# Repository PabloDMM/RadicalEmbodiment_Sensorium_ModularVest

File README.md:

# Sensorium_ModularVest
***Sensorium (Radical Embodiment)*** is a project consisting in a modular illuminated vest that can display abstract information.

***This Repository contains all the files needed to reproduce the device.***
***This Repository is merely destined to the technological part of the project.***
***This Repository makes use of the programs: EagleCad, Arduino IDE, Tensorflow.***

If any other information is needed, please contact with the repository owner (pablodmm.isp@gmail.com) or any of the participants of the project.

## Description

Sensorium is the first prototype for the material tech part of the final project of Gabriel G. Regués. It consist on a modular illuminated vest conformed by an unespecific number of *Arduino* based modules connected to display specific information through an I2C net.

***Watch the Video by pressing the header:***

As escribed in the final essay:

*Sensorium - Radical Embodiment - es un proyecto colectivo desarrollado en colaboración por Jaime Remirez de Ganuza, Gonzalo de Torres Sainz, Pablo de Miguel Morales y Gabriel G. Regües.
Este proyecto es una continuación de un proyecto anterior realizado a finales del 2018 por Jaime y Gabriel, al que llamaron El Culto de la Subversión1 y en el que se formularon algunas preguntas que siguen formando parte de este trabajo. El Culto de la Subversión se enfrentaba a la idea de un grupo social en el que se había impuesto una prenda única y se especulaba sobre las posibilidades de transformación de la misma, a medida que los integrantes entraban o dejaban de formar parte del grupo. Los diseñadores investigaban de qué manera cada individuo podía servir creativamente a la creación de los símbolos de representación de un colectivo organizado de forma igualitaria y horizontal. El proyecto se articuló en torno a la creación de una prenda modular, formada por un número determinado de piezas que podían combinarse de distintas maneras. Estas piezas estaban formadas en tela, en la que habían sido impresos unos elementos gráficos. La posibilidades de reconfiguración de la prenda daban lugar a distintas variaciones, tanto en el aspecto formal como gráfico, que representaban la integración o salida de individuos en el grupo.*

## System Overview

The system is based on a I2C net of *Arduino Nano* based modules that control 10 WS212B RGB LEDs each. The aim is to display abstract information incoming from a *Tensorflow* software system running on a PC based on global population database.

### Arduino Modules

The Arduino Modules are named *IED_GR_Module_Rev_02*. It consist on a triangular PCB equipped with an *Arduino Nano*, a I2C identification resistor array (8bit based, 254 possible directions) and 10 WS2812B RGB LEDs.

Aditionally, it has 3 redundant pairs of miniUSB connectors (both male and female) destined to interconnect an undefined number of modules. The signals present in this connectors are:

* 5V (VCC)
* GND
* SDA (I2C)
* SCL (I2C)

#### Bill of Materials (BOM)
The Module is conformed by the following elements:

* PCB				1	Printed-Circuit-Board	
* Arduino Nano		1	Microprocesador	
* WS2812b  SMD5050	10	RGB LEDs	WS2812B
* Mini USB B female	3	Mini USB B female	
* Mini USB B male	3	Mini USB B male	
* R_DIR_[0:7]		7	10kOhm Resistor. Footprint 1206. Sets the I2C device direction.	
* R_I2C_[0:1]		2	10kOhm Resistor. Footprint 1206. I2C Bus PullUps	

#### PCB Characterictics
The Characteristics of the PCB are the following:

* Dimensions (Square):  100 x 87 mm
* Thickness:            1.6 mm
* Layers:               2 (TOP y BOT)
* Color PCB:            White
* Color Serigraphy:     Black

The PCBs were made through *Elecrow* ( https://www.elecrow.com/ )

#### Prototype Problems
The prototypes have a number of critical mistakes, that can be fixed through the following procedure:

* Step 1: Cut the Signal marked in Blue thorugh the points indicated.
* Step 2: Bypass the signal marked in Green.

Anycase, if anyone plans to rebuild the devices, we strongly encourage to contact us to apply a large number of fixes.

#### Software
The modules make use of two *Arduino* sowfwares, one for *I2C Slave* and another for *I2C Master*:

* _SEN_ModuleI2cMaster.ino_: Distributed a long array of data incoming for USB Serial *Tensorflow* Software running in a PC. Only One module of the net performs as *Master*.

* _SEN_ModuleI2cSlave.ino_: Manages 10 WS2812B REG LEDs based of I2C incoming Data.

Additionally, a large number of preliminary *Arduino* programs can be found in the repository, as part of the development.

Please notice the Arduino Nano used need the *Old ATMega328 Bootloader*, not the new one.

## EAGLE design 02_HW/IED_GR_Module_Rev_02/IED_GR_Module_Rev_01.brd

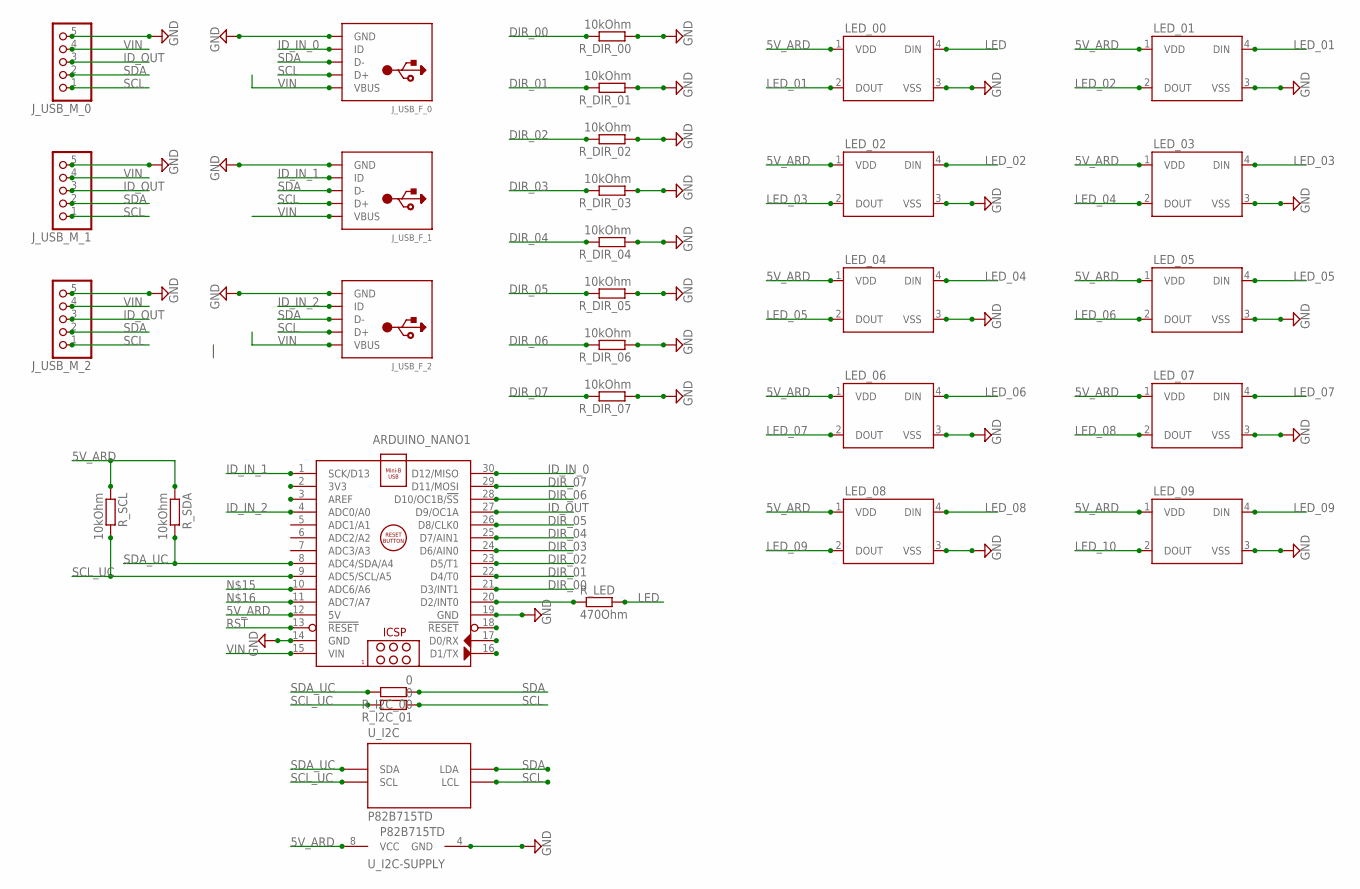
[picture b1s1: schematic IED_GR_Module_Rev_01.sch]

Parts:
ARDUINO_NANO1: ARDUINO_NANO
J_USB_F_0, J_USB_F_1, J_USB_F_2: USBTHM; USB-MINIB-THM
J_USB_M_0, J_USB_M_1, J_USB_M_2: HEADER-1X51.27MM; 1X05_1.27MM
LED_00, LED_01, LED_02, LED_03, LED_04, LED_05, LED_06, LED_07, LED_08, LED_09: WS2812B
R_DIR_00, R_DIR_01, R_DIR_02, R_DIR_03, R_DIR_04, R_DIR_05, R_DIR_06, R_DIR_07: 10kOhm; R1206
R_I2C_00, R_I2C_01: 0; R1206
R_LED: 470Ohm; R1206
R_SCL: 10kOhm; R1206
R_SDA: 10kOhm; R1206
U_I2C: P82B715TD; SOIC-8

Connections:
5V_ARD: ARDUINO_NANO1.12 (5V), LED_00.1 (VDD), LED_01.1 (VDD), LED_02.1 (VDD), LED_03.1 (VDD), LED_04.1 (VDD), LED_05.1 (VDD), LED_06.1 (VDD), LED_07.1 (VDD), LED_08.1 (VDD), LED_09.1 (VDD), R_SCL.1, R_SDA.1, U_I2C.8 (VCC)
DIR_00: ARDUINO_NANO1.21 (D3/INT1), R_DIR_00.2
DIR_01: ARDUINO_NANO1.22 (D4/T0), R_DIR_01.2
DIR_02: ARDUINO_NANO1.23 (D5/T1), R_DIR_02.2
DIR_03: ARDUINO_NANO1.24 (D6/AIN0), R_DIR_03.2
DIR_04: ARDUINO_NANO1.25 (D7/AIN1), R_DIR_04.2
DIR_05: ARDUINO_NANO1.26 (D8/CLK0), R_DIR_05.2
DIR_06: ARDUINO_NANO1.28 (D10/OC1B/!SS), R_DIR_06.2
DIR_07: ARDUINO_NANO1.29 (D11/MOSI), R_DIR_07.2
GND: ARDUINO_NANO1.14 (GND), ARDUINO_NANO1.19 (GND), J_USB_F_0.GND, J_USB_F_1.GND, J_USB_F_2.GND, J_USB_M_0.5, J_USB_M_1.5, J_USB_M_2.5, LED_00.3 (VSS), LED_01.3 (VSS), LED_02.3 (VSS), LED_03.3 (VSS), LED_04.3 (VSS), LED_05.3 (VSS), LED_06.3 (VSS), LED_07.3 (VSS), LED_08.3 (VSS), LED_09.3 (VSS), R_DIR_00.1, R_DIR_01.1, R_DIR_02.1, R_DIR_03.1, R_DIR_04.1, R_DIR_05.1, R_DIR_06.1, R_DIR_07.1, U_I2C.4 (GND)
ID_IN_0: ARDUINO_NANO1.30 (D12/MISO), J_USB_F_0.ID
ID_IN_1: ARDUINO_NANO1.1 (SCK/D13), J_USB_F_1.ID
ID_IN_2: ARDUINO_NANO1.4 (ADC0/A0), J_USB_F_2.ID
ID_OUT: ARDUINO_NANO1.27 (D9/OC1A), J_USB_M_0.3, J_USB_M_1.3, J_USB_M_2.3
LED: LED_00.4 (DIN), R_LED.2
LED_01: LED_00.2 (DOUT), LED_01.4 (DIN)
LED_02: LED_01.2 (DOUT), LED_02.4 (DIN)
LED_03: LED_02.2 (DOUT), LED_03.4 (DIN)
LED_04: LED_03.2 (DOUT), LED_04.4 (DIN)
LED_05: LED_04.2 (DOUT), LED_05.4 (DIN)
LED_06: LED_05.2 (DOUT), LED_06.4 (DIN)
LED_07: LED_06.2 (DOUT), LED_07.4 (DIN)
LED_08: LED_07.2 (DOUT), LED_08.4 (DIN)
LED_09: LED_08.2 (DOUT), LED_09.4 (DIN)
LED_10: LED_09.2 (DOUT)
LED_OUT: ARDUINO_NANO1.20 (D2/INT0), R_LED.1
RST: ARDUINO_NANO1.13 (!RESET)
SCL: J_USB_F_0.D+, J_USB_F_1.D+, J_USB_F_2.D+, J_USB_M_0.1, J_USB_M_1.1, J_USB_M_2.1, R_I2C_01.1, U_I2C.2 (LCL)
SCL_UC: ARDUINO_NANO1.9 (ADC5/SCL/A5), R_I2C_01.2, R_SCL.2, U_I2C.3 (SCL)
SDA: J_USB_F_0.D-, J_USB_F_1.D-, J_USB_F_2.D-, J_USB_M_0.2, J_USB_M_1.2, J_USB_M_2.2, R_I2C_00.1, U_I2C.7 (LDA)
SDA_UC: ARDUINO_NANO1.8 (ADC4/SDA/A4), R_I2C_00.2, R_SDA.2, U_I2C.6 (SDA)
VIN: ARDUINO_NANO1.15 (VIN), J_USB_F_0.VBUS, J_USB_F_1.VBUS, J_USB_F_2.VBUS, J_USB_M_0.4, J_USB_M_1.4, J_USB_M_2.4

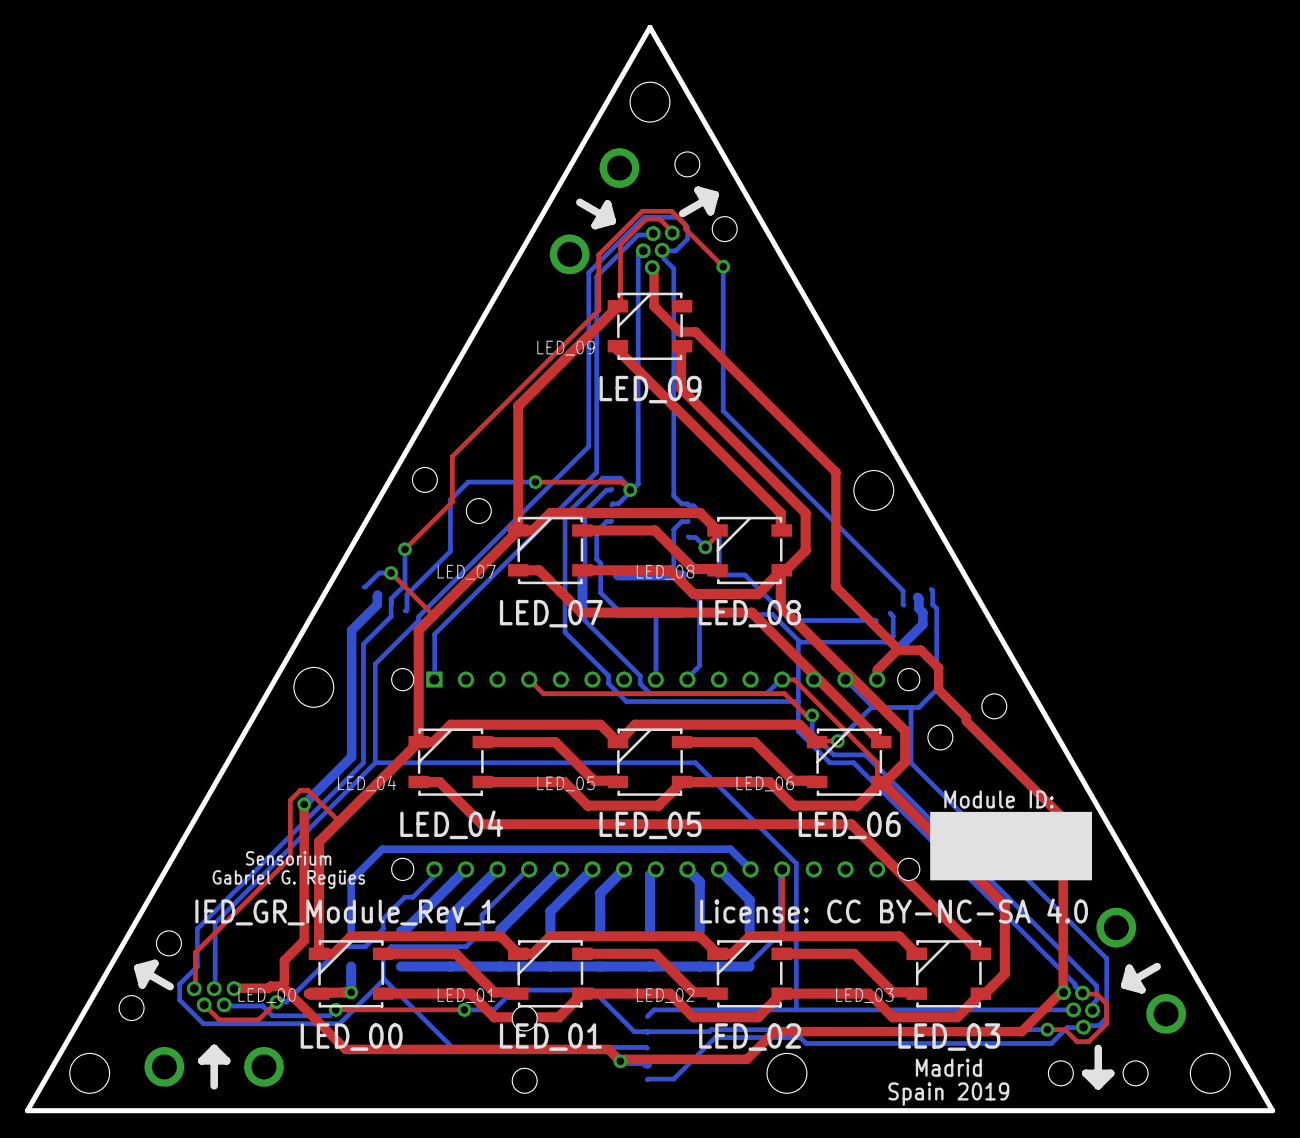
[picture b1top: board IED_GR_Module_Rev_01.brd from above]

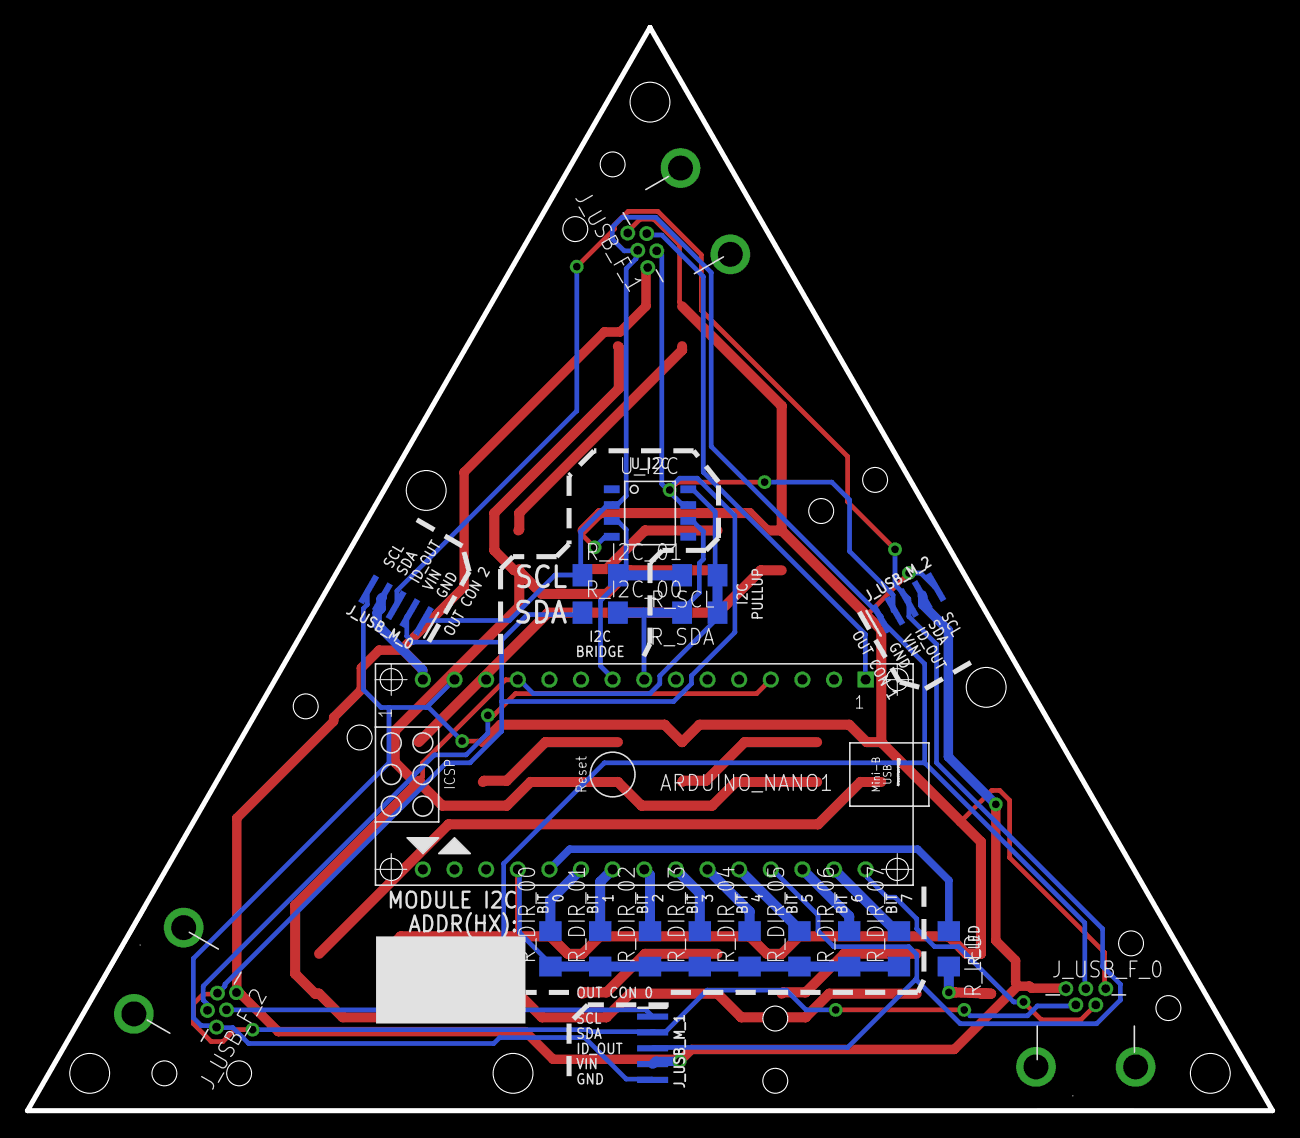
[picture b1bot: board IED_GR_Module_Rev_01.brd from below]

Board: 2 copper layers, 100.0 x 87.0 mm, 31 parts (21 on the bottom side), 30 nets.

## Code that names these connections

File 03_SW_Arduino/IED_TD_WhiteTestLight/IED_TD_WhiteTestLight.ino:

// Libraries
#include <Adafruit_NeoPixel.h>

// Pin definition
const int LED_PIN    = 2;
const int DIR_00_PIN = 3;
const int DIR_01_PIN = 4;
const int DIR_02_PIN = 5;
const int DIR_03_PIN = 6;
const int DIR_04_PIN = 7;
const int DIR_05_PIN = 8;
const int DIR_06_PIN = 10;
const int DIR_07_PIN = 11;

// Program constant values
const int LED_Q      = 10;
// Generated Structures (struct)
struct LEDCOL{
  int red;
  int green;
  int blue;
};
const bool ON                 =   1;         // General ON value
const bool OFF                =   0;         // General OFF value

const bool UP                 =   1;         // General UP Fade Direction value
const bool DOWN               =   0;         // General DOWN Fade Direction value

const int LED_INNER_Q        =   1;         
const int LED_OUTER_Q        =   9;

const int FADESTEPS_C         =   100; // GENERAL FadeSteps
const int FADEDELAY_C         =   100; // GENERAL FadeDelay

const int INNER_LED[LED_INNER_Q]  = {5};
const int OUTER_LED[LED_OUTER_Q]  = {0, 1, 2, 3, 4, 6, 7, 8, 9};

// Gamma Correction (GC) LUT
const byte GC[256] = {
    0,  0,  0,  0,  0,  0,  0,  0,  0,  0,  0,  0,  0,  0,  0,  0,
    0,  0,  0,  0,  0,  0,  0,  0,  0,  0,  0,  0,  1,  1,  1,  1,
    1,  1,  1,  1,  1,  1,  1,  1,  1,  2,  2,  2,  2,  2,  2,  2,
    2,  3,  3,  3,  3,  3,  3,  3,  4,  4,  4,  4,  4,  5,  5,  5,
    5,  6,  6,  6,  6,  7,  7,  7,  7,  8,  8,  8,  9,  9,  9, 10,
   10, 10, 11, 11, 11, 12, 12, 13, 13, 13, 14, 14, 15, 15, 16, 16,
   17, 17, 18, 18, 19, 19, 20, 20, 21, 21, 22, 22, 23, 24, 24, 25,
   25, 26, 27, 27, 28, 29, 29, 30, 31, 32, 32, 33, 34, 35, 35, 36,
   37, 38, 39, 39, 40, 41, 42, 43, 44, 45, 46, 47, 48, 49, 50, 50,
   51, 52, 54, 55, 56, 57, 58, 59, 60, 61, 62, 63, 64, 66, 67, 68,
   69, 70, 72, 73, 74, 75, 77, 78, 79, 81, 82, 83, 85, 86, 87, 89,
   90, 92, 93, 95, 96, 98, 99,101,102,104,105,107,109,110,112,114,
  115,117,119,120,122,124,126,127,129,131,133,135,137,138,140,142,
  144,146,148,150,152,154,156,158,160,162,164,167,169,171,173,175,
  177,180,182,184,186,189,191,193,196,198,200,203,205,208,210,213,
  215,218,220,223,225,228,231,233,236,239,241,244,247,249,252,255 };

LEDCOL GEN_ON    = {GC[255], GC[255],  GC[255]};  
LEDCOL GEN_OFF   = {GC[0],   GC[0],     GC[0]}; 


// Global Variables
Adafruit_NeoPixel LEDSTR = Adafruit_NeoPixel(LED_Q, LED_PIN, NEO_GRB + NEO_KHZ800);
bool fadeDirection = UP;


// IMPORTANT: To reduce NeoPixel burnout risk, add 1000 uF capacitor across
// pixel power leads, add 300 - 500 Ohm resistor on first pixel's data input
// and minimize distance between Arduino and first pixel.  Avoid connecting
// on a live circuit...if you must, connect GND first.

void setup() {
  Serial.begin(115200); // Baudrate Set
  LEDSTR.begin();
  LEDSTR.show(); // Initialize all pixels to 'off'
}

void loop() {
  for(int currentStep = 0; currentStep < FADESTEPS_C; currentStep++){
    LED_GLOWOUT(GEN_ON, GEN_OFF, FADESTEPS_C, (FADEDELAY_C/5), currentStep, fadeDirection);
  }
  fadeDirection = !fadeDirection;   // Switch Fade Glow Direction
}

void LED_GLOWOUT(LEDCOL COL_ON, LEDCOL COL_OFF, int FS, int FD, int Step, bool fadeDir){
  int RDiff = (COL_OFF.red-COL_ON.red);
  int GDiff = (COL_OFF.green-COL_ON.green);
  int BDiff = (COL_OFF.blue-COL_ON.blue);
  //for(int Step = 0; Step < FS; Step++){
  if(fadeDir == UP){
    for(int i = 0; i < LED_INNER_Q; i++){
      //Serial.println(i);
      LEDSTR.setPixelColor(INNER_LED[i], (COL_OFF.green - ((GDiff/FS)*(FS-Step))), (COL_OFF.red - ((RDiff/FS)*(FS-Step))), (COL_OFF.blue - ((BDiff/FS)*(FS-Step))));
    }
    for(int i = 0; i < LED_OUTER_Q; i++){
      //Serial.println(i);
      LEDSTR.setPixelColor(OUTER_LED[i], (COL_OFF.green - ((GDiff/FS)*(Step))), (COL_OFF.red - ((RDiff/FS)*(Step))), (COL_OFF.blue - ((BDiff/FS)*(Step))));
    }
    LEDSTR.show(); // Update LEDs 
    delay(FD);
  }

  else if(fadeDir == DOWN){
    for(int i = 0; i < LED_INNER_Q; i++){
      //Serial.println(i);
      LEDSTR.setPixelColor(INNER_LED[i], (COL_OFF.green - ((GDiff/FS)*(Step))), (COL_OFF.red - ((RDiff/FS)*(Step))), (COL_OFF.blue - ((BDiff/FS)*(Step))));
    }
    for(int i = 0; i < LED_OUTER_Q; i++){
      //Serial.println(i);
      LEDSTR.setPixelColor(OUTER_LED[i], (COL_OFF.green - ((GDiff/FS)*(FS-Step))), (COL_OFF.red - ((RDiff/FS)*(FS-Step))), (COL_OFF.blue - ((BDiff/FS)*(FS-Step))));
    }
    LEDSTR.show(); // Update LEDs 
    delay(FD);
  }
}

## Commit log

2019-10-31 First Readme Release
    First Readme Release, still to be completed.
2019-10-31 Second Update of Readme
    Added some formatting
2019-10-31 Update Readme
    Thrid Update fo the Readme with some more information.
2019-10-31 Upload of Project Files
    Upload of all the local project files containing both SW and HW, as well as documentation.
2019-10-31 Update Readme
    Fourth Update, adding Images.
2019-10-31 Image Upload
    Upload of images for documentation.
2019-11-01 Updae Readme
    Fitfth and provisional final update of the Readme Description file

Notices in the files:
02_HW/IED_GR_Module_Rev_02/IED_GR_Module_Rev_01.brd:
License: CC BY-NC-SA 4.0
02_HW/IED_GR_Module_Rev_02/IED_GR_Module_Rev_01.sch:
CC BY-NC-SA 4.0
parts and their libraries:
SparkFun-LED: Licensing: Creative Commons ShareAlike 4.0 International - https://creativecommons.org/licenses/by-sa/4.0
microbuilder: This work is placed in the public domain, and may be freely used for commercial and non-commercial work with the following conditions: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
